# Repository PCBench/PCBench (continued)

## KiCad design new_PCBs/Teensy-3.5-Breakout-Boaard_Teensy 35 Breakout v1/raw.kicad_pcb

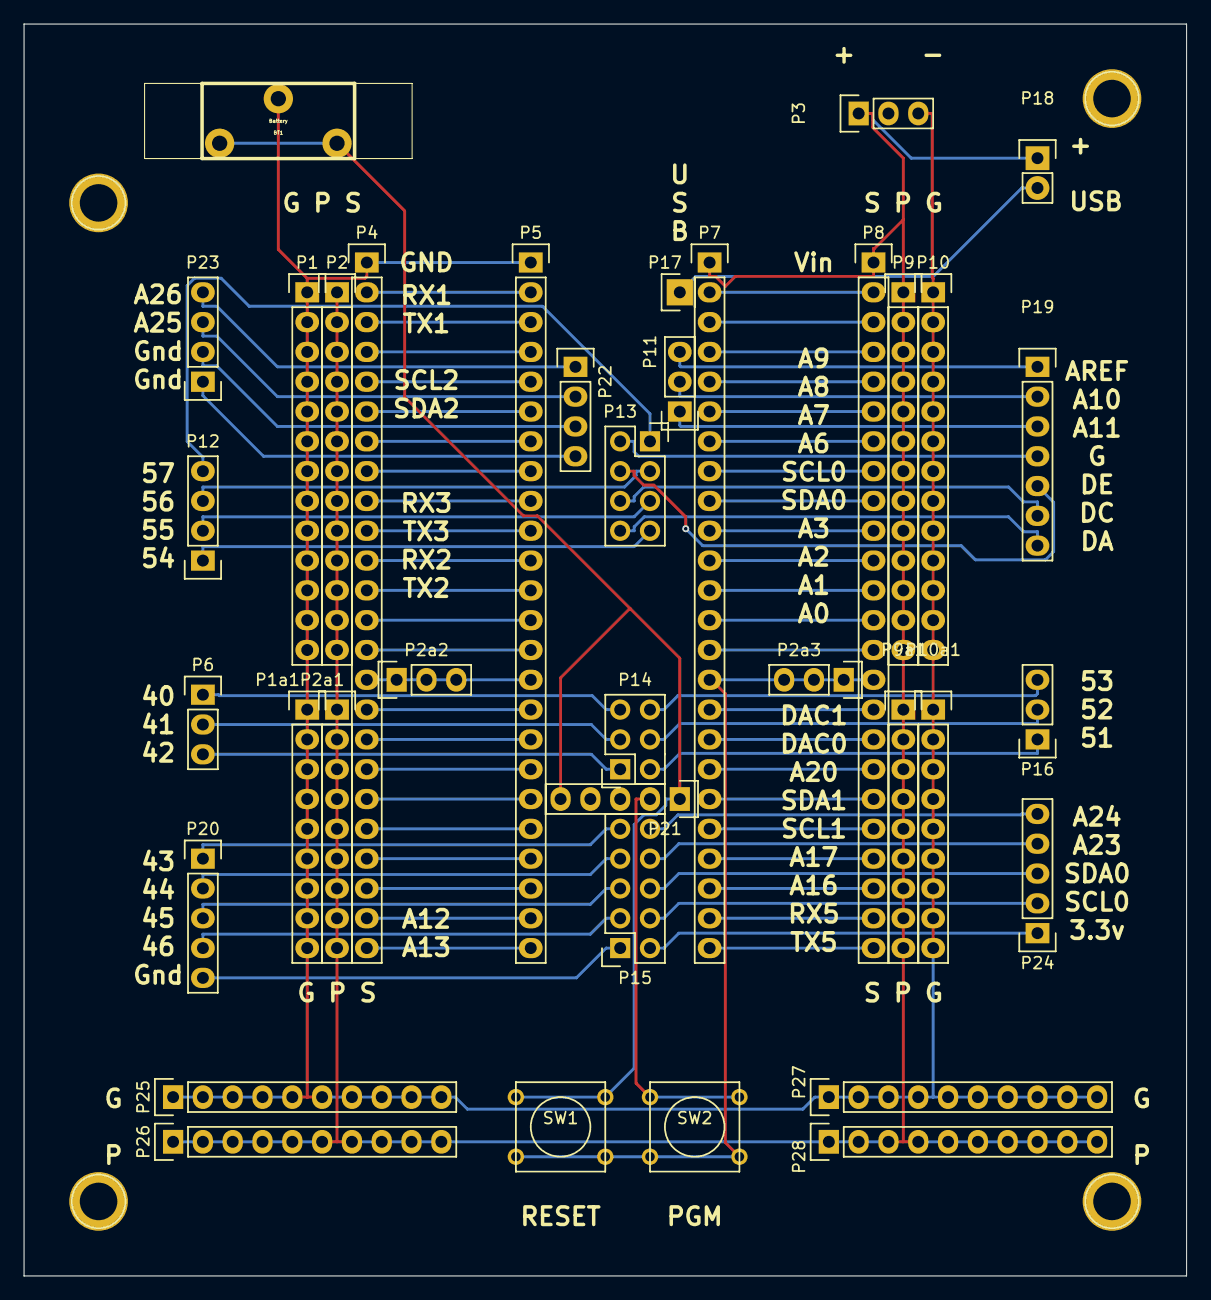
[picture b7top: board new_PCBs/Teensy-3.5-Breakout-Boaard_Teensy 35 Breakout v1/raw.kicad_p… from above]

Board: 2 copper layers, 99.1 x 106.7 mm, 41 parts (0 on the bottom side), 83 nets.

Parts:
BT1: Battery; BAT_HOLDER_2032
P1, P2, P9, P10: CONN_01X13; Pin_Header_Straight_1x13
P1a1, P2a1, P9a1: CONN_01X09; Pin_Header_Straight_1x09
P2a2, P2a3, P3, P6, P16: CONN_01X03; Pin_Header_Straight_1x03
P4, P8: CONN_01X24; Pin_Header_Straight_1x24
P5, P7: CONN_01X24; Socket_Strip_Straight_1x24
P10a1: CONN_01X10; Pin_Header_Straight_1x09
P11: CONN_01X03; Socket_Strip_Straight_1x03
P12, P23: CONN_01X04; Pin_Header_Straight_1x04
P13: CONN_02X04; Socket_Strip_Straight_2x04
P14: CONN_02X03; Socket_Strip_Straight_2x03
P15: CONN_02X05; Socket_Strip_Straight_2x05
P17: CONN_01X01; Socket_Strip_Straight_1x01
P18: CONN_01X02; Pin_Header_Straight_1x02
P19: CONN_01X08; Pin_Header_Straight_1x07
P20, P24: CONN_01X05; Pin_Header_Straight_1x05
P21: CONN_01X05; Socket_Strip_Straight_1x05
P22: CONN_01X04; Socket_Strip_Straight_1x04
P25, P26, P27, P28: CONN_01X10; Pin_Header_Straight_1x10
RE4: 1pin
REF1, REF2, REF3: 1pin
SW1, SW2: SW_PUSH_SMALL_H; SW_PUSH_SMALL

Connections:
unnamed: BT1.1, P21.5
unnamed: BT1.2, P1.1, P1.2, P1.3, P1.4, P1.5, P1.6, P1.7, P1.8, P1.9, P1.10, P1.11, P1.12, P1.13, P1a1.1, P1a1.2, P1a1.3, P1a1.4, P1a1.5, P1a1.6, P1a1.7, P1a1.8, P1a1.9, P3.3, P4.1, P5.1, P10.1, P10.2, P10.3, P10.4, P10.5, P10.6, P10.7, P10.8, P10.9, P10.10, P10.11, P10.12, P10.13, P10a1.1, P10a1.2, P10a1.3, P10a1.4, P10a1.5, P10a1.6, P10a1.7, P10a1.8, P10a1.9, P25.1, P25.2, P25.3, P25.4, P25.5, P25.6, P25.7, P25.8, P25.9, P25.10, P27.1, P27.2, P27.3, P27.4, P27.5, P27.6, P27.7, P27.8, P27.9, P27.10
unnamed: P2a2.1, P2a2.2, P2a2.3, P4.15, P5.15
unnamed: P2a3.1, P2a3.2, P2a3.3, P7.15, P8.15, SW1.2, SW2.2
unnamed: P4.2, P5.2
unnamed: P4.3, P5.3
unnamed: P4.4, P5.4
unnamed: P4.5, P5.5
unnamed: P4.6, P5.6
unnamed: P4.7, P5.7
unnamed: P4.8, P5.8
unnamed: P4.9, P5.9
unnamed: P4.10, P5.10
unnamed: P4.11, P5.11
unnamed: P4.12, P5.12
unnamed: P4.13, P5.13
unnamed: P4.14, P5.14
unnamed: P4.16, P5.16
unnamed: P4.17, P5.17
unnamed: P4.18, P5.18
unnamed: P4.19, P5.19
unnamed: P4.20, P5.20
unnamed: P4.21, P5.21
unnamed: P4.22, P5.22
unnamed: P4.23, P5.23
unnamed: P4.24, P5.24
unnamed: P7.2, P8.2
unnamed: P7.3, P8.3
unnamed: P7.4, P8.4
unnamed: P7.5, P8.5
unnamed: P7.6, P8.6
unnamed: P7.7, P8.7
unnamed: P7.8, P8.8
unnamed: P7.9, P8.9
unnamed: P7.10, P8.10
unnamed: P7.11, P8.11
unnamed: P7.12, P8.12
unnamed: P7.13, P8.13
unnamed: P7.14, P8.14
unnamed: P7.16, P8.16
unnamed: P7.17, P8.17
unnamed: P7.18, P8.18
unnamed: P7.19, P8.19
unnamed: P7.20, P8.20
unnamed: P7.21, P8.21
unnamed: P7.22, P8.22
unnamed: P7.23, P8.23
unnamed: P7.24, P8.24
unnamed: P11.1, P19.3
unnamed: P11.2, P19.2
unnamed: P11.3, P19.1
unnamed: P12.1, P13.7
unnamed: P12.2, P13.5
unnamed: P12.3, P13.3
unnamed: P12.4, P13.1
unnamed: P13.2, P19.4
unnamed: P13.4, P19.5
unnamed: P13.6, P19.6
unnamed: P13.8, P19.7
unnamed: P6.3, P14.1
unnamed: P14.2, P16.1
unnamed: P6.2, P14.3
unnamed: P14.4, P16.2
unnamed: P6.1, P14.5
unnamed: P14.6, P16.3
unnamed: P15.1, P20.5
unnamed: P15.2, P24.1
unnamed: P15.3, P20.4
unnamed: P15.4, P24.2
unnamed: P15.5, P20.3
unnamed: P15.6, P24.3
unnamed: P15.7, P20.2
unnamed: P15.8, P24.4
unnamed: P15.9, P20.1
unnamed: P15.10, P24.5
unnamed: P17.1, P18.2
unnamed: P2.1, P2.2, P2.3, P2.4, P2.5, P2.6, P2.7, P2.8, P2.9, P2.10, P2.11, P2.12, P2.13, P2a1.1, P2a1.2, P2a1.3, P2a1.4, P2a1.5, P2a1.6, P2a1.7, P2a1.8, P2a1.9, P3.1, P8.1, P9.1, P9.2, P9.3, P9.4, P9.5, P9.6, P9.7, P9.8, P9.9, P9.10, P9.11, P9.12, P9.13, P9a1.1, P9a1.2, P9a1.3, P9a1.4, P9a1.5, P9a1.6, P9a1.7, P9a1.8, P9a1.9, P18.1, P26.1, P26.2, P26.3, P26.4, P26.5, P26.6, P26.7, P26.8, P26.9, P26.10, P28.1, P28.2, P28.3, P28.4, P28.5, P28.6, P28.7, P28.8, P28.9, P28.10
unnamed: P21.1, SW1.1
unnamed: P21.2, SW2.1
unnamed: P22.1, P23.4
unnamed: P22.2, P23.3
unnamed: P22.3, P23.2
unnamed: P22.4, P23.1

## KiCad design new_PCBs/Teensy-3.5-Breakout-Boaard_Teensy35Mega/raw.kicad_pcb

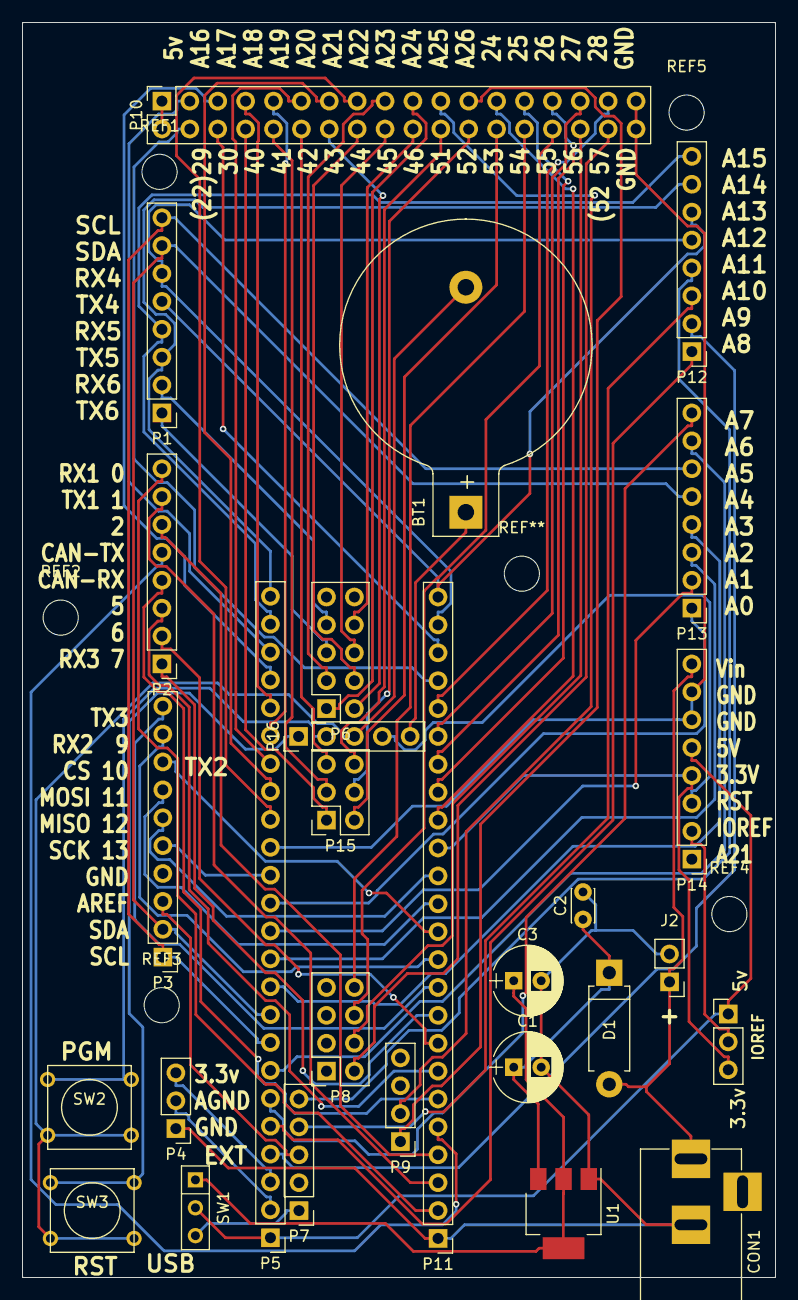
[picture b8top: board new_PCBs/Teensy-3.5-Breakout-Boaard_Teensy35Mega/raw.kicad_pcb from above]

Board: 2 copper layers, 68.6 x 114.3 mm, 33 parts (0 on the bottom side), 82 nets.

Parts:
BT1: BATTERY; Keystone_103_1x20mm-CoinCell
C1, C3: CP; CP_Radial_D6.3mm_P2.50mm
C2: C; C_Disc_D3.0mm_W2.0mm_P2.50mm
CON1: BARREL_JACK
D1: D_Small; D_DO-15_P10.16mm_Horizontal
J1: CONN_01X03; Pin_Header_Straight_1x03_Pitch2.54mm
J2: CONN_01X02; Pin_Header_Straight_1x02_Pitch2.54mm
P1, P2, P12, P13, P14: CONN_01X08; Socket_Strip_Straight_1x08_Pitch2.54mm
P3: CONN_01X10; Socket_Strip_Straight_1x10_Pitch2.54mm
P4: CONN_01X03; Pin_Header_Straight_1x03_Pitch2.54mm
P5, P11: CONN_01X24; Socket_Strip_Straight_1x24_Pitch2.54mm
P6: CONN_02X05; Socket_Strip_Straight_2x05_Pitch2.54mm
P7, P16: CONN_01X05; Socket_Strip_Straight_1x05_Pitch2.54mm
P8: CONN_02X04; Socket_Strip_Straight_2x04_Pitch2.54mm
P9: CONN_01X04; Socket_Strip_Straight_1x04_Pitch2.54mm
P10: CONN_02X18; Socket_Strip_Straight_2x18_Pitch2.54mm
P15: CONN_02X03; Socket_Strip_Straight_2x03_Pitch2.54mm
REF1, REF2, REF3, REF4, REF5: MountingHole_3.2mm_M3_ISO14580_Pad; MountingHole_3.2mm_M3
SW1: PWR SEL; SW_Micro_SPST
SW2: PGM; SW_PUSH_SMALL
SW3: RST; SW_PUSH_SMALL
U1: NCP1117ST50T3G_MountingTab; SOT-223

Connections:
unnamed: BT1.1, P16.5
unnamed: BT1.2, P16.3, SW2.2, SW3.2
unnamed: C1.1, C2.1, D1.1, U1.3
unnamed: C1.2, C2.2, C3.2, CON1.2, J2.2, P4.1, P11.1, U1.1
unnamed: C3.1, SW1.1, U1.2, U1.4
unnamed: CON1.1, D1.2, J2.1, P14.8
unnamed: J1.1, P5.1, P14.5, SW1.2
unnamed: J1.2, P14.2
unnamed: J1.3, P11.15, P14.4
unnamed: P1.1, P6.5
unnamed: P1.2, P6.7
unnamed: P1.3, P5.24, P12.7
unnamed: P1.4, P5.23, P12.8
unnamed: P1.5, P11.24, P12.6
unnamed: P1.6, P11.23, P12.5
unnamed: P1.7, P3.2, P5.9, P13.5
unnamed: P1.8, P3.1, P5.8, P13.6
unnamed: P3.3, P7.3
unnamed: P3.5, P5.14
unnamed: P4.2, P5.2
unnamed: P4.3, P5.3
unnamed: P7.1, SW1.3
unnamed: P10.1, P10.2
unnamed: P5.22, P10.3
unnamed: P10.4, P11.21
unnamed: P5.21, P10.5
unnamed: P10.6, P11.22
unnamed: P5.20, P10.7
unnamed: P10.8, P15.1
unnamed: P5.19, P10.9
unnamed: P10.10, P15.3
unnamed: P5.18, P10.11
unnamed: P10.12, P15.5
unnamed: P5.17, P10.13
unnamed: P6.2, P10.14
unnamed: P5.16, P10.15
unnamed: P6.4, P10.16
unnamed: P6.3, P10.17
unnamed: P6.6, P10.18
unnamed: P6.1, P10.19
unnamed: P6.8, P10.20
unnamed: P9.2, P10.21
unnamed: P10.22, P15.6
unnamed: P9.1, P10.23
unnamed: P10.24, P15.4
unnamed: P10.25, P11.16
unnamed: P10.26, P15.2
unnamed: P10.27, P11.17
unnamed: P8.8, P10.28
unnamed: P10.29, P11.18
unnamed: P8.6, P10.30
unnamed: P10.31, P11.19
unnamed: P8.4, P10.32
unnamed: P10.33, P11.20
unnamed: P8.2, P10.34
unnamed: P5.15, P10.35, P10.36, P14.6, P14.7
unnamed: P2.8, P11.2
unnamed: P2.7, P11.3
unnamed: P2.6, P11.4
unnamed: P2.5, P11.5
unnamed: P2.4, P11.6
unnamed: P2.3, P11.7
unnamed: P2.2, P11.8
unnamed: P2.1, P11.9
unnamed: P3.10, P11.10
unnamed: P3.9, P11.11
unnamed: P3.8, P11.12
unnamed: P3.7, P11.13
unnamed: P3.6, P11.14
unnamed: P5.5, P12.1
unnamed: P5.4, P12.2
unnamed: P7.4, P12.3
unnamed: P7.5, P12.4
unnamed: P5.13, P13.1
unnamed: P5.12, P13.2
unnamed: P5.11, P13.3
unnamed: P5.10, P13.4
unnamed: P5.7, P13.7
unnamed: P5.6, P13.8
unnamed: P14.3, P16.4
unnamed: P16.1, SW3.1
unnamed: P16.2, SW2.1
